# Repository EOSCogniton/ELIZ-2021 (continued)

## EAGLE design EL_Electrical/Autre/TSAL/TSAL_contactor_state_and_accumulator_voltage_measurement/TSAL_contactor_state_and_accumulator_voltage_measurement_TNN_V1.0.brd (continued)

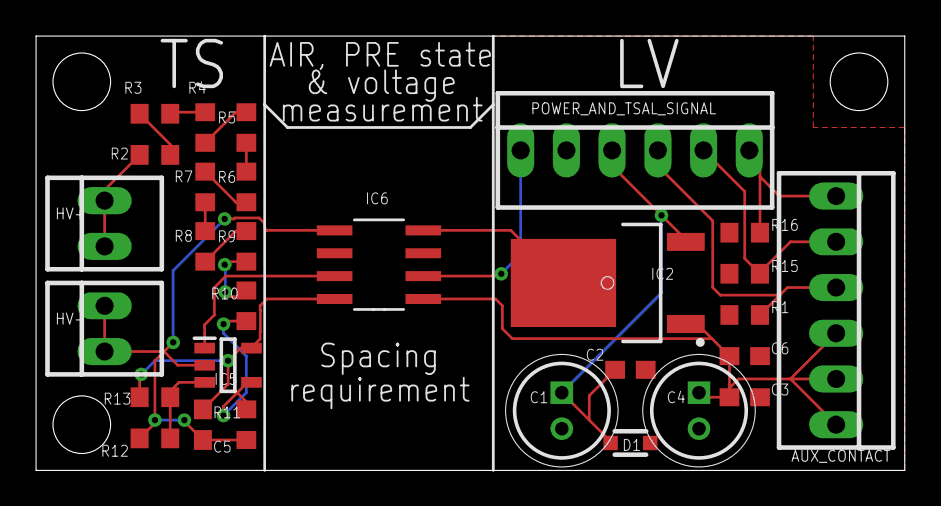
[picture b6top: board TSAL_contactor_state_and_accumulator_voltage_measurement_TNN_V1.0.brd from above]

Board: 2 copper layers, 48.3 x 24.1 mm, 29 parts (0 on the bottom side), 21 nets.

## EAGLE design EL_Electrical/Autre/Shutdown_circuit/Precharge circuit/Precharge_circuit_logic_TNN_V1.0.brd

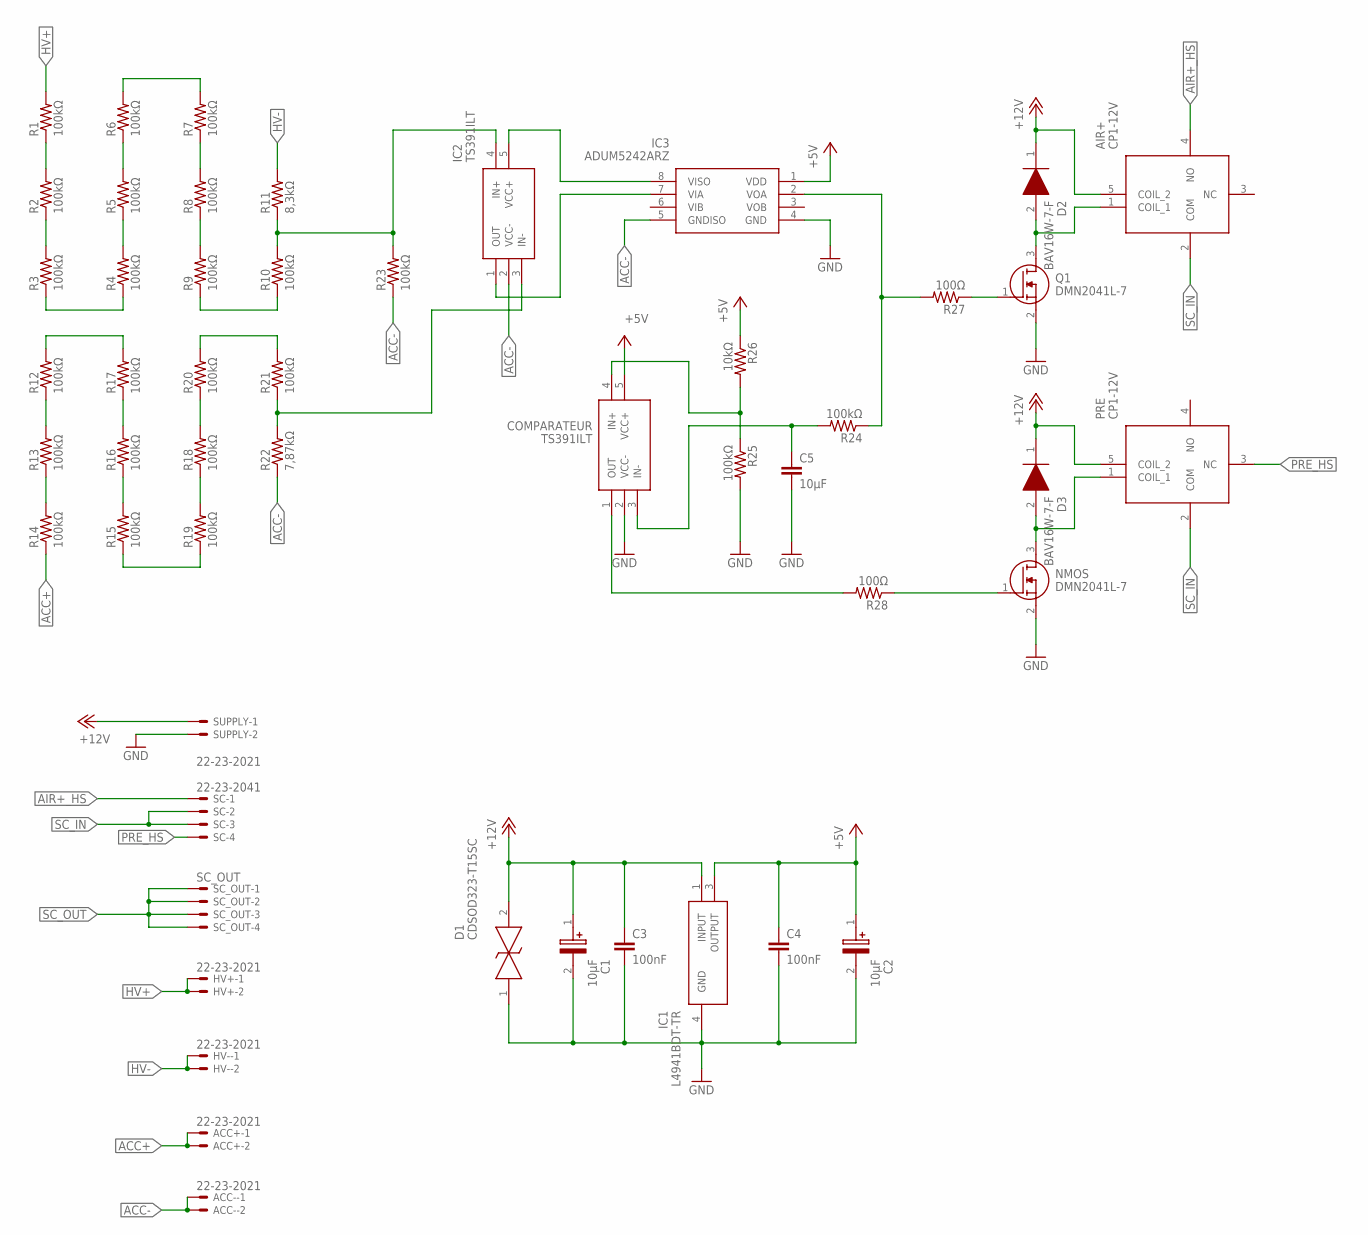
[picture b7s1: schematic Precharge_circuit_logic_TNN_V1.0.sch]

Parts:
ACC+: 22-23-2021
ACC-: 22-23-2021
AIR+: CP1-12V; CP1FORMC_1
C1, C2: 10μF; CAPPRD200W55D525H1200
C3, C4: 100nF; C0603
C5: 10μF; C0603
COMPARATEUR: TS391ILT; SOT95P280X145-5N
D1: CDSOD323-T15SC; SOD-323
D2, D3: BAV16W-7-F; SOD3716X145N
HV+: 22-23-2021
HV-: 22-23-2021
IC1: L4941BDT-TR; TO228P972X240-3N
IC2: TS391ILT; SOT95P280X145-5N
IC3: ADUM5242ARZ; SOIC127P600X175-8N
NMOS: DMN2041L-7; SOT96P240X110-3N
PRE: CP1-12V; CP1FORMC_1
Q1: DMN2041L-7; SOT96P240X110-3N
R1, R2, R3, R4, R5, R6, R7, R8, R9, R10, R12, R13, R14, R15, R16, R17, R18, R19, R20, R21, R23, R24, R25: 100kΩ; R0603
R11: 8,3kΩ; R0603
R22: 7,87kΩ; R0603
R26: 10kΩ; R0603
R27, R28: 100Ω; R0603
SC: 22-23-2041
SC_OUT: SC_OUT; 22-23-2041
SUPPLY: 22-23-2021

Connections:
+5V: C2.1 (+), C4.1, COMPARATEUR.5 (VCC+), IC1.3 (OUTPUT), IC3.1 (VDD), R26.1
+12V: AIR+.5 (COIL_2), C1.1 (+), C3.1, D1.2, D2.1 (K), D3.1 (K), IC1.1 (INPUT), PRE.5 (COIL_2), SUPPLY.1
ACC+: ACC+.1, ACC+.2, R14.1
ACC-: ACC-.1, ACC-.2, IC2.2 (VCC-), IC3.5 (GNDISO), R22.1, R23.1
AIR+_HS: AIR+.4 (NO), SC.1
GND: C1.2 (-), C2.2 (-), C3.2, C4.2, C5.2, COMPARATEUR.2 (VCC-), D1.1, IC1.4 (GND), IC3.4 (GND), NMOS.2 (S), Q1.2 (S), R25.2, SUPPLY.2
HV+: HV+.1, HV+.2, R1.2
HV-: HV-.1, HV-.2, R11.2
unnamed: R1.1, R2.2
unnamed: R2.1, R3.2
unnamed: R3.1, R4.1
unnamed: R4.2, R5.1
unnamed: R5.2, R6.1
unnamed: R6.2, R7.2
unnamed: R7.1, R8.2
unnamed: R8.1, R9.2
unnamed: R9.1, R10.1
unnamed: IC2.4 (IN+), R10.2, R11.1, R23.2
unnamed: IC2.5 (VCC+), IC3.8 (VISO)
unnamed: COMPARATEUR.4 (IN+), R25.1, R26.2
unnamed: R13.1, R14.2
unnamed: R12.1, R13.2
unnamed: R12.2, R17.2
unnamed: R16.2, R17.1
unnamed: R15.2, R16.1
unnamed: R15.1, R19.1
unnamed: R18.1, R19.2
unnamed: R18.2, R20.1
unnamed: R20.2, R21.2
unnamed: IC2.3 (IN-), R21.1, R22.2
unnamed: D3.2 (A), NMOS.3 (D), PRE.1 (COIL_1)
unnamed: IC2.1 (OUT), IC3.7 (VIA)
unnamed: C5.1, COMPARATEUR.3 (IN-), R24.2
unnamed: IC3.2 (VOA), R24.1, R27.2
unnamed: COMPARATEUR.1 (OUT), R28.2
unnamed: AIR+.1 (COIL_1), D2.2 (A), Q1.3 (D)
unnamed: NMOS.1 (G), R28.1
unnamed: Q1.1 (G), R27.1
PRE_HS: PRE.3 (NC), SC.4
SC_IN: AIR+.2 (COM), PRE.2 (COM), SC.2, SC.3
SC_OUT: SC_OUT.1, SC_OUT.2, SC_OUT.3, SC_OUT.4

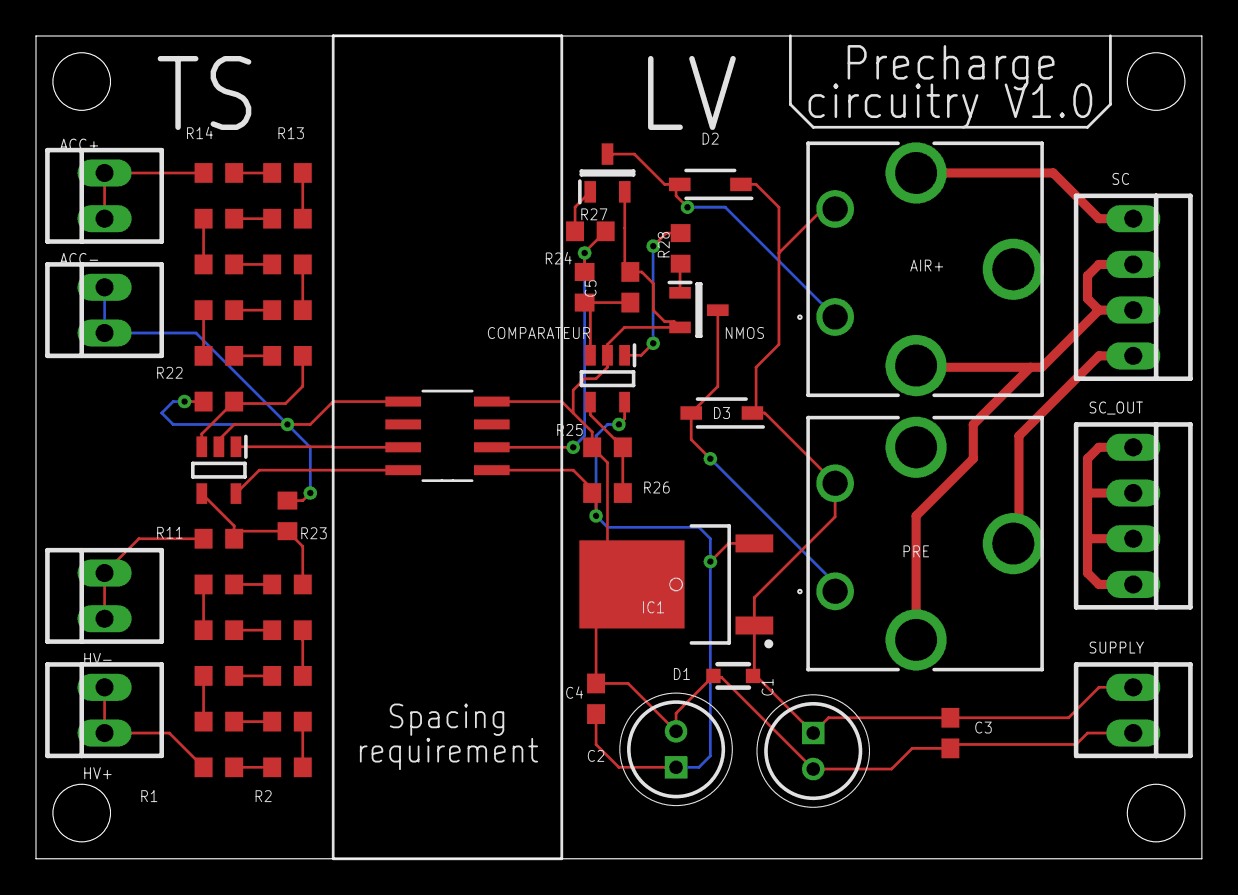
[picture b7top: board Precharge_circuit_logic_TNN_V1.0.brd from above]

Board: 2 copper layers, 64.8 x 45.7 mm, 51 parts (0 on the bottom side), 41 nets.

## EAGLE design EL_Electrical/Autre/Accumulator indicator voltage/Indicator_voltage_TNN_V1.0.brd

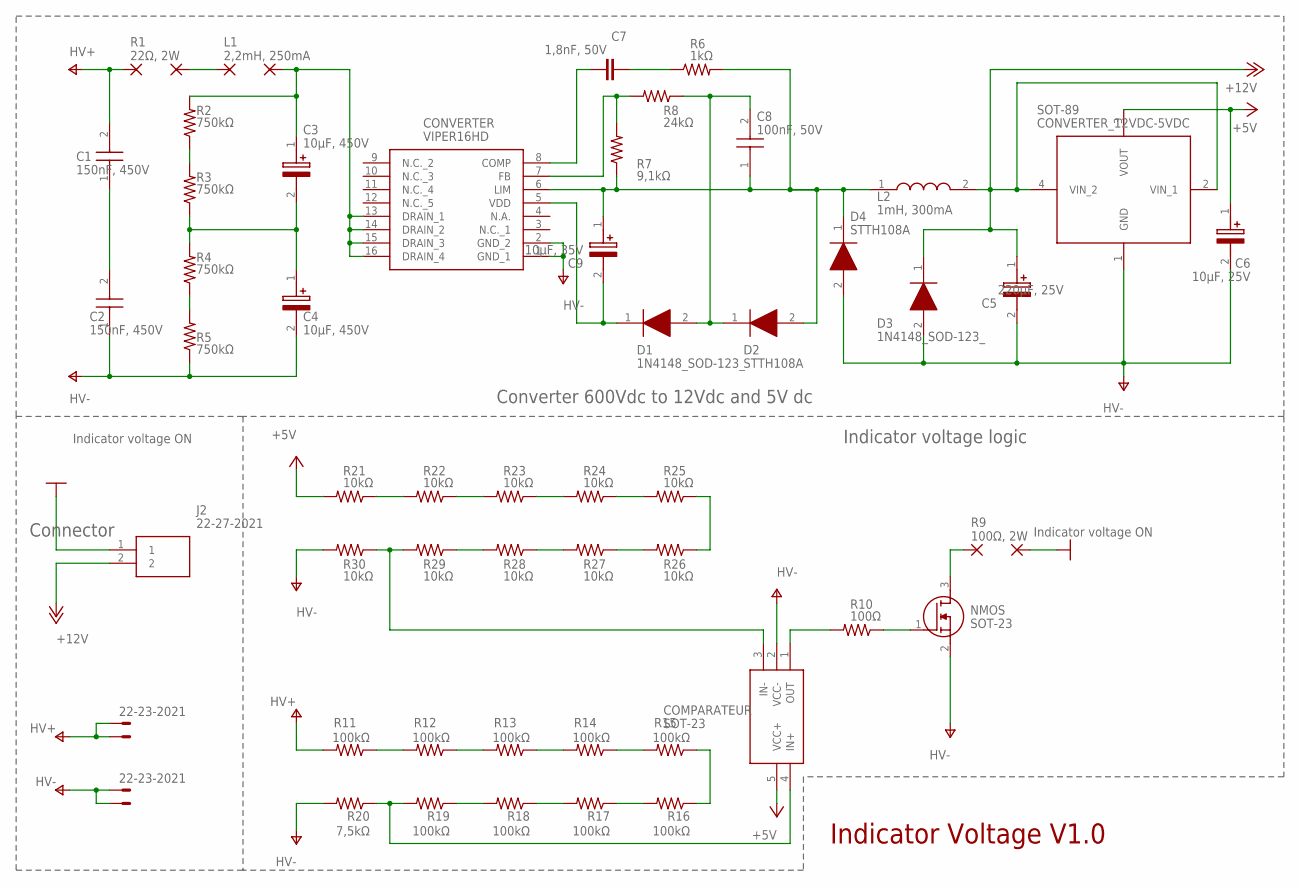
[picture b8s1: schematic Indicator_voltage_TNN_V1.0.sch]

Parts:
C1, C2: 150nF, 450V; CAPC4720X175N
C3, C4: 10μF, 450V; CAPPRD500W60D1300H2250
C5: 220μF, 25V; CAPPRD500W60D1300H2250
C6: 10μF, 25V; CAPPRD200W55D525H1200
C7: 1,8nF, 50V; C0805
C8: 100nF, 50V; CAPC2012X88N
C9: 10μF, 35V; CAPPRD200W55D525H1200
COMPARATEUR: SOT-23; SOT95P280X145-5N
CONVERTER: VIPER16HD; SOIC127P600X175-16N
CONVERTER_12VDC-5VDC: SOT-89; ST-SOT-89
D1, D3: 1N4148_SOD-123_; SOD3716X135N
D2, D4: STTH108A; DIOM5126X265N
HV+: 22-23-2021
HV-: 22-23-2021
J2: 22-27-2021; SHDR2W64P0X254_1X2_508X580X117
L1, L3: 2,2mH, 250mA; 1,6/0,8
L2: 1mH, 300mA; RLB0914
NMOS: SOT-23; SOT96P240X110-3N
PAD2, PAD4: 1,6/0,8
R1: 22Ω, 2W; 1,6/0,8
R2, R3, R4, R5: 750kΩ; M3216
R6: 1kΩ; M2012
R7: 9,1kΩ; M2012
R8: 24kΩ; M2012
R9: 100Ω, 2W; 1,6/0,8
R10: 100Ω; R0603
R11, R12, R13, R14, R15, R16, R17, R18, R19: 100kΩ; R0603
R20: 7,5kΩ; R0603
R21, R22, R23, R24, R25, R26, R27, R28, R29, R30: 10kΩ; R0603

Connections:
0V: J2.1, PAD4.1
+5V: C6.1 (+), COMPARATEUR.5 (VCC+), CONVERTER_12VDC-5VDC.3 (VOUT), R21.2
+12V: C5.1 (+), CONVERTER_12VDC-5VDC.2 (VIN_1), CONVERTER_12VDC-5VDC.4 (VIN_2), D3.1 (K), J2.2, L2.2
unnamed: R11.1, R12.2
unnamed: L1.1, PAD2.1
unnamed: C9.2 (-), CONVERTER.5 (VDD), D1.1 (K)
unnamed: C1.1, C2.2
unnamed: C3.1 (+), CONVERTER.13 (DRAIN_1), CONVERTER.14 (DRAIN_2), CONVERTER.15 (DRAIN_3), CONVERTER.16 (DRAIN_4), L3.1, R2.2
unnamed: R4.1, R5.2
unnamed: C3.2 (-), C4.1 (+), R3.1, R4.2
unnamed: R2.1, R3.2
unnamed: C7.2, CONVERTER.8 (COMP)
unnamed: C7.1, R6.1
unnamed: C8.1, C9.1 (+), CONVERTER.6 (LIM), D2.2 (A), D4.1 (K), L2.1, R6.2, R7.1
unnamed: C8.2, D1.2 (A), D2.1 (K), R8.1
unnamed: R12.1, R13.2
unnamed: CONVERTER.7 (FB), R7.2, R8.2
unnamed: R13.1, R14.2
unnamed: R14.1, R15.2
unnamed: R15.1, R16.1
unnamed: R16.2, R17.1
unnamed: R17.2, R18.1
unnamed: R18.2, R19.1
unnamed: COMPARATEUR.4 (IN+), R19.2, R20.1
unnamed: COMPARATEUR.1 (OUT), R10.2
unnamed: R21.1, R22.2
unnamed: R22.1, R23.2
unnamed: R23.1, R24.2
unnamed: R24.1, R25.2
unnamed: R25.1, R26.1
unnamed: R26.2, R27.1
unnamed: R27.2, R28.1
unnamed: R28.2, R29.1
unnamed: COMPARATEUR.3 (IN-), R29.2, R30.1
unnamed: NMOS.3 (D), R9.1
unnamed: NMOS.1 (G), R10.1
V+: C1.2, HV+.1, HV+.2, R1.1, R11.2
V-: C2.1, C4.2 (-), C5.2 (-), C6.2 (-), COMPARATEUR.2 (VCC-), CONVERTER.1 (GND_1), CONVERTER.2 (GND_2), CONVERTER_12VDC-5VDC.1 (GND), D3.2 (A), D4.2 (A), HV-.1, HV-.2, NMOS.2 (S), R5.1, R20.2, R30.2

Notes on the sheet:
Converter 600Vdc to 12Vdc and 5V dc
Indicator voltage logic
Connector
Indicator Voltage V1.0

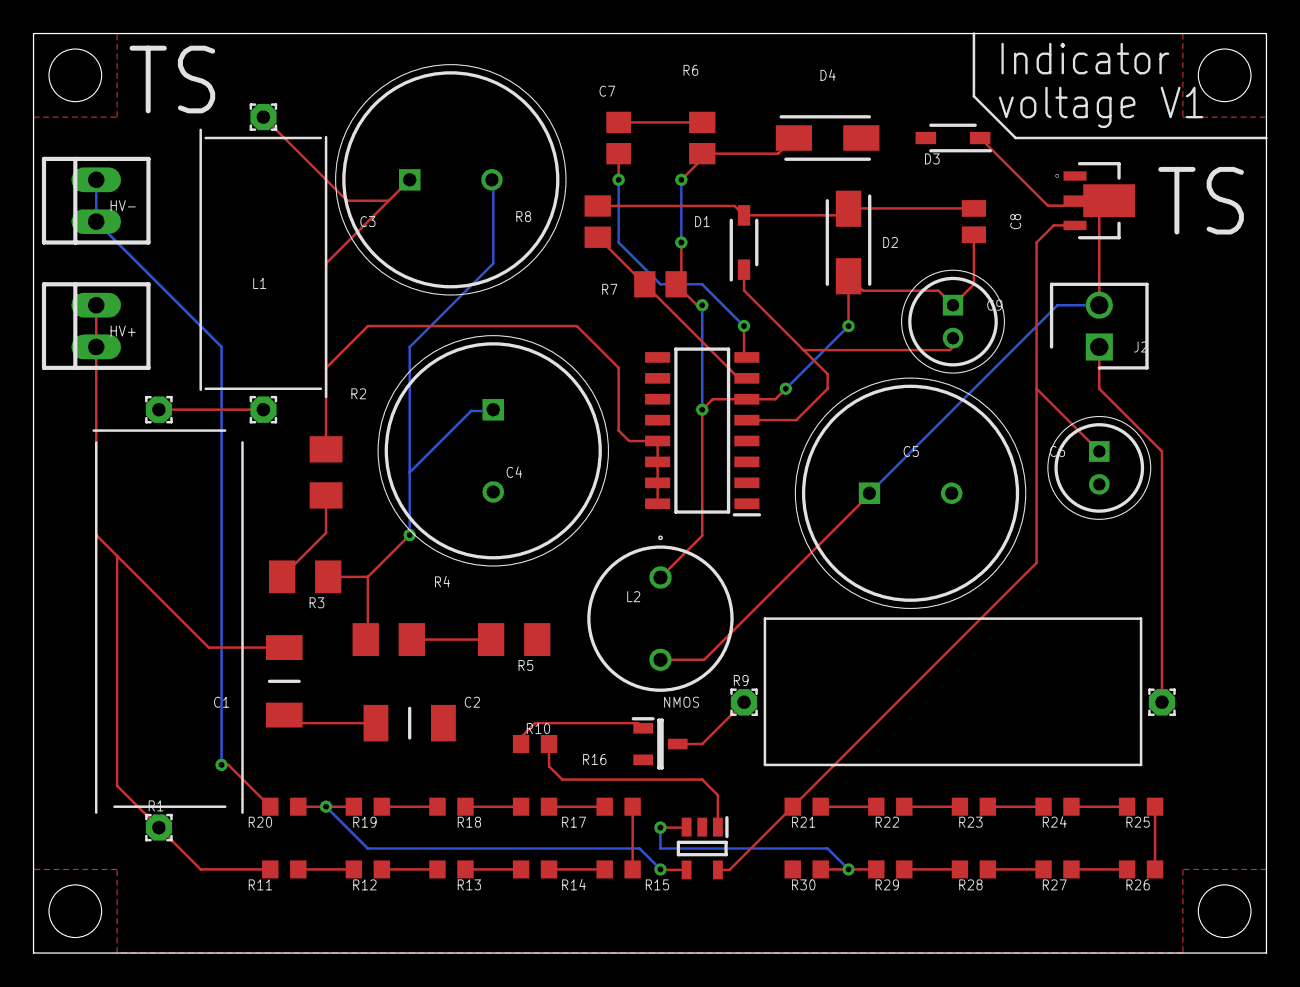
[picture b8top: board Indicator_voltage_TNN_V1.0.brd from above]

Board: 2 copper layers, 74.9 x 55.9 mm, 55 parts (0 on the bottom side), 38 nets.

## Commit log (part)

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2022-02-09 MEP LaFabrique
2022-02-13 Maj Frame
2022-02-15 Pour Guillaue v4
2022-02-16 MaJ MeP frame
2022-02-16 V1 Mep Container mounting
2022-02-16 Ajout fente carte SD
2022-02-16 Auto stash before rebase of "origin/master"
    Support LV
2022-02-16 Fente carte SD
2022-02-16 Correction
2022-02-16 Maj Placement TdB
2022-02-16 Etanchéité support écran
2022-02-16 Ajout support écran en stp
2022-02-17 Auto stash before merge of "master" and "origin/master"
2022-02-20 Avancée code VCU
2022-02-21 Modifs code vcu
2022-02-23 Conversions et améliorations code VCU
2022-03-01 maj vcu
2022-03-02 Rectification chape
2022-03-02 Gabarit Engine
2022-03-02 Gabarit firewall
2022-03-02 update gabarit firewall
2022-03-02 meps lm prod / centrale
2022-03-02 Rectif chape
2022-03-08 ajout gabarits
2022-03-08 Gabarit baquet-harness
2022-03-08 Ajout Electrical System Form
2022-03-09 Maj gabarit baquet-harness
2022-03-09 MEP Gabarit Engine
2022-03-09 gabarit carrosserie haut
2022-03-09 up gabarit firewall
2022-03-09 consignes impression gabarit
2022-03-09 gabarit chasea
2022-03-09 Gabarit Engine changement
2022-03-11 LV Battery support + gabarit appui tete
2022-03-11 Placement batterie LV
2022-03-13 Gabarit_SU
2022-03-14 ha clairement c la merde la
2022-03-14 suite_Gabarit_SU
2022-03-15 changement SU
2022-03-15 Gabarit_arriere
2022-03-16 Ajout APPS
2022-03-16 proto plaque renfort TS/TSAC protection
2022-03-16 gabarit
2022-03-16 Gabarit pedalier
2022-03-17 esf apps
2022-03-17 esf segment dta
2022-03-17 GabaritSuspension
2022-03-17 maj Gabarit_suspension
2022-03-17 gabarit carrosserie
2022-03-17 gabarit floorpan
2022-03-18 ESF Shutdown Circuit
2022-03-18 ESF accumulator
2022-03-19 ESF charging and TS Schematics
2022-03-21 ESF maj
2022-03-21 ESF maj2
2022-03-21 Ajout template ESF
2022-03-21 Ajout Abrevation ESF
2022-03-21 Ajout system overview (sans la schematic)
2022-03-21 ESF ajout Shutdown Circuit concept 2.1.1
2022-03-21 ESF SC wiring
2022-03-21 ESF ajout IMD
2022-03-21 ESF ajout inertia switch
2022-03-22 floorpan gabarit
2022-03-22 SU Gabarits
2022-03-22 carrosserie gabarit
2022-03-22 maj esf
2022-03-23 Rectif chapes SU
2022-03-23 MAJ Suspension
2022-03-23 Auto stash before rebase of "origin/master"
2022-03-23 gabarit suspension avant
2022-03-23 ESF_181
2022-03-23 ESF IMD
2022-03-23 Modif gabarit suspension
2022-03-23 ESF ajout Shutdown Circuit
2022-03-24 ESF SC expliation terminé
2022-03-24 ESF maj firewall ACE
2022-03-24 ESF Indicator voltage
2022-03-24 ESF charger, accumulator, grounding
2022-03-24 list of components of accumulator
2022-03-24 MAJ Format
2022-03-29 gabarit accel
2022-03-29 Maj gabarits SU
2022-03-29 plaques renfort chassis v2
2022-03-29 chapes EL
2022-03-29 Gabarit triangle avant bas
2022-03-29 Gravure sur gabarit_SU
2022-03-29 MAJ gabarit_SU
2022-03-30 Gabarit pince arrière
2022-03-30 MAJ gabarit pince arrière
2022-03-30 MAJ MEP Gabarits SU
2022-03-31 Ajout gabarit BAR et steering
2022-04-05 Prod gabarit fablab
2022-06-08 MAJ cost finale
2022-07-04 MEP cylindre throttle pedal pdf
2022-07-04 reparation lien cassé elec
2022-07-04 MEP Appui tete
2022-07-04 MEP Torsion Bar
2022-07-04 MEP Chapes Oubli Elec
2022-07-04 conversion igs
2022-07-05 Creation MEP manquante
2022-07-06 suite MEPs EL
2022-07-17 ajout stp batterie
2022-07-18 upper container electronics maj
2022-07-18 upper container add souriau connector
2022-07-18 add battery tyva v2 stp
2022-07-21 add rendu batterie tyva v2
2022-09-09 Ajout gabarit basculeur AV
2022-09-27 Modif chape basculeur AV
2022-09-28 Actualisation
2022-09-28 Commande
2022-09-28 Mise en plan dossier mache
2022-09-28 Commandes
2022-09-30 Reprise MEP pour La Mache
2022-10-01 Insert triangle V2
2022-10-03 Auto stash before rebase of "origin/master"
    Actualisation
2022-10-03 Footrest
2022-10-04 Ajout ancienne version TSAL ZZG
2022-10-06 chapes mep carrosserie/LV
2022-10-13 MEP direction+Suspension
2022-11-01 Recopie de FR_04016
2022-11-04 MEP de pièces de pédalier
2022-11-10 Relecture MEP QLC
2022-11-14 Ajout MEP pour La Mache
2022-11-14 MEP Chape TdB
2022-11-14 MEP Chapes TdB
2022-11-14 Ajout cote
2022-11-14 tolerances mep
2022-11-14 MEP de 2 chapes EL
2022-11-14 EL_06008
2022-11-15 ajout gabarit
2022-11-15 Verif MEP + Container mounting point
2022-11-15 Gabarit decoupe
2022-11-15 Ajout Gabarit direction + MEP fabrique
2022-11-15 Support batterie v3
2022-11-15 Support Batterie v3.0
2022-11-15 Support battterie v3.1
2022-11-15 Support batterie v3.2
2022-11-16 re-upload de EL_05001
2022-11-16 Ajout chape brakelight
2022-11-16 MEP Chape Brake Light
2022-11-16 Ré-organisation Dossier Brake Light
2022-11-22 Gabarit MS bis
2022-11-23 Gabarit tr av bas et direction
2022-11-23 Gabarit TdB début
2022-11-23 Gabarit TdB v2
2022-11-24 MEP gabarit MS bis
2022-11-29 Fin mep gabarit
2022-11-30 gabarits triangles arrières
2022-11-30 assembly avec triangles arrères
2022-11-30 ajout MEP gabarit triangles arrières
2022-12-07 Gabarit collage+MEP la fabrique igs
2022-12-07 Remise Cylinder screw distribution
2022-12-07 Ajout support grille
2022-12-12 gabarit collage AR
2022-12-15 MEP gabarit collage
2022-12-31 Brake Pedal BOTS
2022-12-31 Duplication du pédalier et ajout de la frame d'Invictus
2023-01-04 mise en place du nouveau système de fixation du BOTS
2023-01-04 J'avais oublié ces pièces de la fixation BOTS
2023-01-04 MEP FR_03015
2023-01-04 MEP FR_03001_9
2023-01-08 Nouvelle version Pédale avec BOTS
2023-01-10 MEP collage
2023-01-10 Pièces boisard
2023-01-10 Pédalier
2023-01-10 Mise en place support BOTS
2023-01-10 Support 1 BOTS
2023-01-11 MEP pedalier
2023-01-11 Enregistrement support 1
2023-01-11 Enregistrement support 2
2023-01-11 Ajout assemblage BOTS 1
2023-01-11 modif 1 MEP (tolérances)
2023-01-11 MEP Boisard
2023-01-11 Ajout des 2 versions du BOTS
2023-01-12 Réglage Position
2023-01-12 Résolution pièces cachées BOTS
2023-01-12 Boisard
2023-01-16 MEP la mache laser
2023-01-16 MAJ MEP gorge du loup
2023-01-16 Kill switch gabarit
2023-01-16 Finition réglage BOTS
2023-02-01 Placement boitiers LV - TSAL, BSPD, FuseBox
2023-02-01 Placement VCU
2023-02-01 Enregistrement des MEPs de la batterie HV en format PDF
2023-02-01 MEP BOTS Valkyriz
2023-02-01 Mise à jour trous dashboard
    Corrections trous du dashboard
2023-02-21 Ajout cartouche EPSA MEP
2023-02-22 Cale Moyeu
2023-02-22 cale Front brake disc
2023-02-25 Handcart design
2023-02-25 Handcart_final_touches
2023-02-25 visserie handcart
2023-02-27 Finalisation visserie Handcart
2023-02-28 Modification distribution brake cylinder
2023-03-05 Fin de rémi madness
2023-03-05 Retour de la LAS
2023-03-05 Rajout de la dernière pièce de merde
2023-03-07 Début design upper_container busbars
2023-03-07 SES FSG Valkyriz
2023-03-09 Ajout save code_TDN
2023-03-14 Rear busbar design
2023-03-14 Design busbars v1
    Crétion de deux pièces busbar dans upper containes
2023-03-14 Bussbar visserie
2023-03-14 SES + qqs MEP non pushées
2023-03-15 images SES
2023-03-15 Vues SES
2023-03-15 legende tube
2023-03-15 SES meca
2023-03-16 SES suite accumulator
2023-03-16 ses accumulator mounting point
2023-03-16 tubes qui apparaissaient pas
2023-03-16 compliance crashbox
2023-03-16 idem
2023-03-16 il m'a fait un truc chelou mais c'est bon
2023-03-16 word à transformer en pdf (/!\ incomplet /!\)
2023-03-16 Simus container mounting point + SES
2023-03-16 Ajout vis 1
2023-03-16 Ajout vis batterie
2023-03-17 Modif lower container + simus
2023-03-17 Mise à jour lower container avec support + vis M8 + SES finis pour Container Attachment
2023-03-17 Ajout de la facture de la crashbox
2023-03-17 gestion crise crashbox
2023-03-17 Fin crise
2023-03-17 Finalisation SES
2023-03-17 IAD et SE3D
2023-03-17 SE3D igs avec les tubes
2023-03-17 SE3D
2023-03-21 datasheet crashbox
2023-03-21 epaisseur aip
2023-03-23 IAD v2
2023-03-28 brake axle tread
2023-03-28 Ajout changement LAS
2023-03-30 Auto stash before rebase of "origin/master"
    MEP pour caisson batterie bois
2023-03-30 MEP caisson bois
2023-04-04 Plan d'ensemble prote moyeu + moyeu
2023-04-26 Support pompe + quelques modifs show/hide
2023-05-10 SES Review QLC
2023-05-11 IAD final version
2023-05-11 Rectification cover sheet ses
2023-05-13 Mofids ses
2023-05-14 Correction ses EV5 et EV5.5
    Correction partie batterie pour satisfaire les juges
2023-05-14 Modif SES
2023-05-14 Fin SES v2
2023-05-17 SES v3 1e version (+ ajout de points sur la TP)
2023-05-20 Cales rotules v1
2023-05-21 Cales rotules v2
2023-05-21 Cales rotules v3
2023-05-22 Cales rotules v4
2023-05-22 Cales rotules v5
2023-05-23 mep usinage arbre de transmission
2023-05-23 Cales rotules v6
2023-05-24 Cales rotules v7
2023-05-25 Water Pump v1
2023-05-27 Nettoyage maquette (aïe) v1
2023-05-28 Alignement EN avec la maquette
2023-05-28 Nettoyage maquette (aïe) v2
2023-05-28 Ça nettoie fort
2023-05-28 Nettoyage encore
2023-05-28 Nettoyage et archéologie de dingueries
2023-05-28 Support TS Box
2023-05-29 TS Box, BAMOCAR, câbles
    Je crois que je vais mourir jeune
2023-06-01 Petits ajustements maquette
2023-06-02 Refroidissement encore
2023-06-02 SES v3.2 - non fini
2023-06-04 Nettoyage maquette encore
2023-06-06 Câbles circuit de refroidissement
2023-06-06 Câbles circuit de refroidissement 2
    J'ai fait un câble en trois heures et il était pas au bon endroit. Une bonne productivité finalement.
2023-06-07 Câbles circuit de refroidissement 3
    C'est le début d'une grande aventure
2023-06-07 CABLES
2023-06-09 CABLES 2
    Vraiment tout ça pour ça, c'est honteux
2023-06-09 Quelques ajouts
    Je fais plus d'EPSA pour les six prochaines semaines allez
2023-06-10 MEPs EDR
    Ajout du dossier EDR avec MEPs, drawings et PDF de l'EDR 2023
2023-06-12 Modif txt
    Modifications mineures de fichiers txt
2023-06-17 SES v3.3
2023-06-19 SES v3.4 (f)
2023-08-13 Modification sur le fichier "Nomenclature"
2023-10-10 Modification Chapes EN
2023-10-24 chapes SU
2023-10-24 chapes SU congés
2023-10-24 Ahah je suis une branche
2023-10-24 Revert "Ahah je suis une branche"
    This reverts commit 1d6451782a1d9b069bb7d48dd950595e2812da3c.
2023-10-25 Chapes SU suite
2023-10-25 discard
2023-10-25 chape SU encore
2023-10-25 chapes Rocker formation
2023-10-25 mise en plan de Chape_RRocker_R
2023-11-08 MEP Frocker
2023-11-08 rangement dossier chapes SU
2023-11-08 Modif Rocker f
2023-11-08 Modif chape + mep rocker
2023-11-08 deplac
2023-11-08 mise en plan chapes
2023-11-12 Rangement + modification chapes EN
    modification des rayons exterieur pour respecter la règle T10.1.4 pour Engine
2023-11-12 Chapes basculeur avant et roll bar
    ajout du travail de Samuel (SEM)
2023-11-12 rectification R_Rocker_R
2023-11-29 Test RBX
2023-11-29 Ajout capuchon rotule
2023-12-05 montage serré gabarits
2023-12-05 test
2023-12-05 Gabarit arriere bas serré
2023-12-05 gabarit arrière haut serré
2023-12-05 gabarit avant bas serré
2023-12-05 gabarit avant haut serré
2023-12-21 Travail suspensions
2024-01-04 Mesures sur la batterie TYVA
2024-01-24 Revert "Mesures sur la batterie TYVA"
    This reverts commit 2e26c1a6a5b55764fcba92f8e7dcb7fd7e12b945.
2024-01-30 Revert "Auto stash before merge of "master" and "origin/master""
    This reverts commit 2e9067c702981155eec5676b5724e46116ad0a90.
2024-01-30 Ajout du système TSAC
2024-02-06 Assemblages contraints (WT)
2024-02-07 modif insert arrière haut
2024-02-11 modifs mal pointés
2024-02-20 susp
2024-03-04 de tout pas important
2024-03-06 modif découpe laser
2024-03-12 prepa gabarits en 5mm pour Artemiz
2024-03-12 prod La Fabrique
2024-03-13 Auto stash before rebase of "origin/master"
    modif mineur front brake caliper
2024-04-02 gabarit chapes harnais
2024-05-28 Gabarits SU_14011 et ST_04003
2025-02-18 Modifs support moteur
    Retouches support moteur gauche et MEP 1
2025-05-22 shields
    modifs shield chaine et moteur
2025-05-23 modifs shields
    modifs pour ajouter casing moteur/nouveau protège chaine
    c'est très mal rangé attention
